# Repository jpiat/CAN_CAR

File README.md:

# CAN_CAR
Project for a RC car modded to be a mockup of a CAN bus for a real car

SCAD directory contains 3D models used for the motor encoder and parts mounting platform
PCB directory contains PCB designs for the Teensy CAN adapter and Arduin pro mini CAN adapter
SW directory contains code for both the CAN peripherals and main control unit

The main brain of the car is a Beaglebone green fitted with a CAN bus cape from Waveshare. The motor and steering servo control is performed by a teensy 3.1/2 fitted with a custom CAN board. Additional control units (collision sensors, headlights ...) will be added using arduino pro mini with CAN adapter.
The goal is to easily add sub-systems on the CAN bus to add functions ilke :
- line crossing detection
- vision-based road sign reading
- ...

Car base used for this project :
http://www.hobbyking.com/hobbyking/store/__24971__Turnigy_Trooper_SCT_4x4_1_10_Brushless_Short_Course_Truck_ARR_.html

The brushless motor and ESC are removed and replaced with a brushed 540 motor with H-bridge (easier to get full control of the motor)

H-bridge driver for the brushed motor

https://www.pololu.com/product/706 (cheaper eBay equivalent)

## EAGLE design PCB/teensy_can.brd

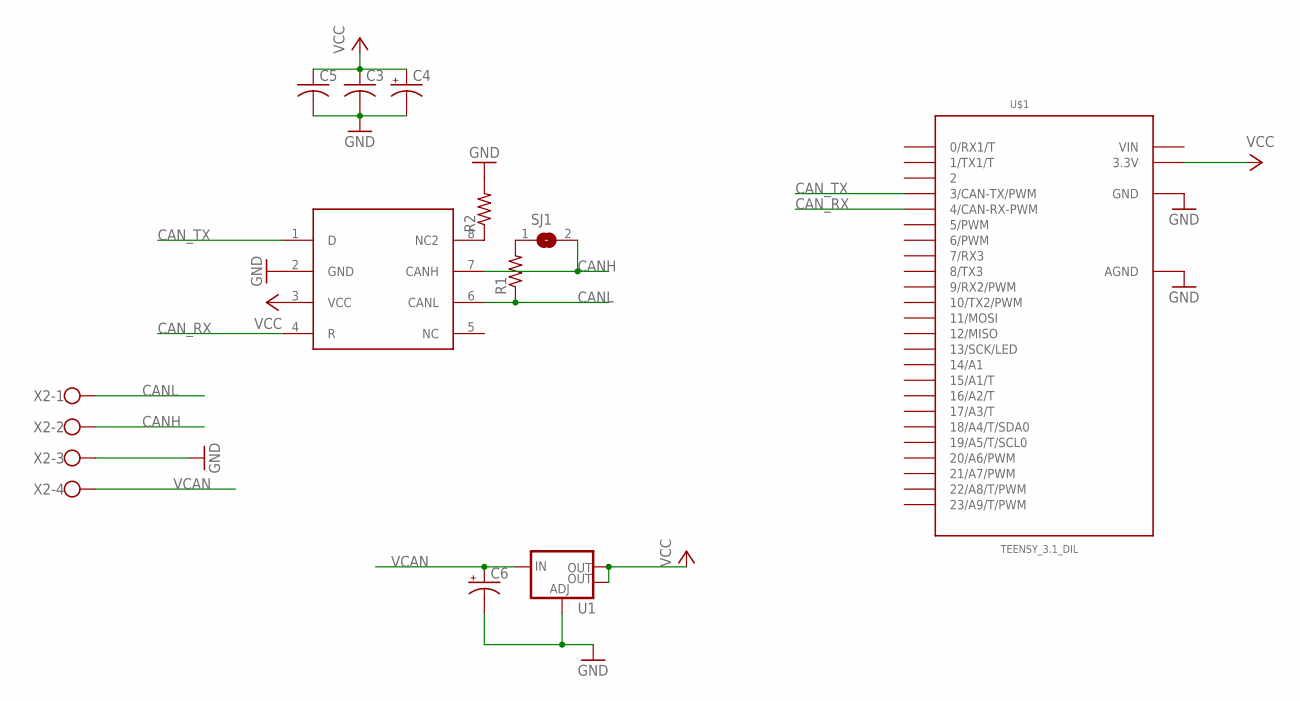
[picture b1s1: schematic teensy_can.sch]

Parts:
C3, C5: C-USC0805K; C0805K
C4, C6: CPOL-USA/3216-18R; A/3216-18R
R1, R2: R-US_R0805; R0805
SJ1: SJ
U1: V_REG_LM1117SOT223; SOT223
U$1: TEENSY_3.1_DIL; TEENSY3-DIL
U$2: SN65HVD232; SO08-SKINNYPADS
X2: W237-4

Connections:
CANH: SJ1.2, U$2.7 (CANH), X2.2
CANL: R1.1, U$2.6 (CANL), X2.1
CAN_RX: U$1.4 (4/CAN-RX-PWM), U$2.4 (R)
CAN_TX: U$1.3 (3/CAN-TX/PWM), U$2.1 (D)
GND: C3.2, C4.-, C5.2, C6.-, R2.2, U1.1 (ADJ), U$1.AGND, U$1.GND, U$2.2 (GND), X2.3
unnamed: R1.2, SJ1.1
unnamed: R2.1, U$2.8 (NC2)
VCAN: C6.+, U1.3 (IN), X2.4
VCC: C3.1, C4.+, C5.1, U1.2 (OUT), U1.4 (OUT), U$1.3.3V, U$2.3 (VCC)
VIN: U$1.VIN

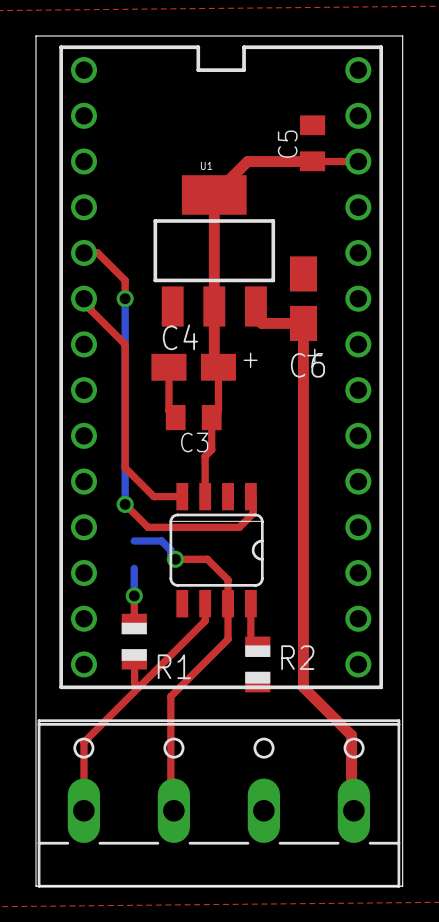
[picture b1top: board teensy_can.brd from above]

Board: 2 copper layers, 20.4 x 47.2 mm, 11 parts (1 on the bottom side), 9 nets.

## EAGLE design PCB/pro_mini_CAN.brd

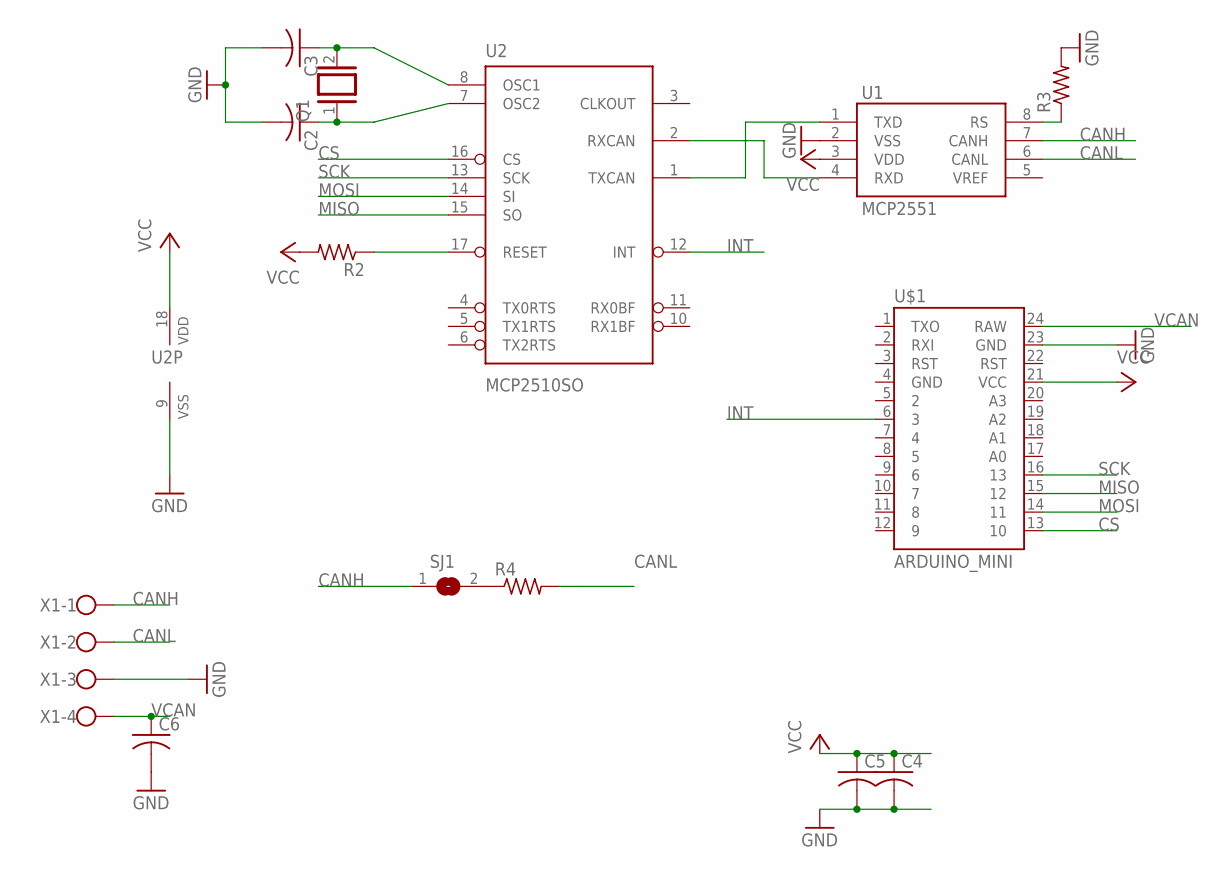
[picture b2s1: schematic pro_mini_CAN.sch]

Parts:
C2, C3, C4, C5, C6: C-USC0805K; C0805K
Q1: XTAL/S; QS
R2, R3, R4: R-US_R0805; R0805
SJ1: SJ
U1: MCP2551; SO08
U2: MCP2510SO; SO-18W
U$1: ARDUINO_MINI
X1: W237-4

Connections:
CANH: SJ1.1, U1.7 (CANH), X1.1
CANL: R4.2, U1.6 (CANL), X1.2
CS: U2.16 (CS), U$1.13 (10)
GND: C2.2, C3.2, C4.2, C5.2, C6.2, R3.2, U1.2 (VSS), U2.9 (VSS), U$1.23 (GND), X1.3
INT: U2.12 (INT), U$1.6 (3)
MISO: U2.15 (SO), U$1.15 (12)
MOSI: U2.14 (SI), U$1.14 (11)
unnamed: C3.1, Q1.2, U2.8 (OSC1)
unnamed: C2.1, Q1.1, U2.7 (OSC2)
unnamed: U1.1 (TXD), U2.1 (TXCAN)
unnamed: U1.4 (RXD), U2.2 (RXCAN)
unnamed: R2.1, U2.17 (RESET)
unnamed: R3.1, U1.8 (RS)
unnamed: R4.1, SJ1.2
SCK: U2.13 (SCK), U$1.16 (13)
VCAN: C6.1, U$1.24 (RAW), X1.4
VCC: C4.1, C5.1, R2.2, U1.3 (VDD), U2.18 (VDD), U$1.21 (VCC)

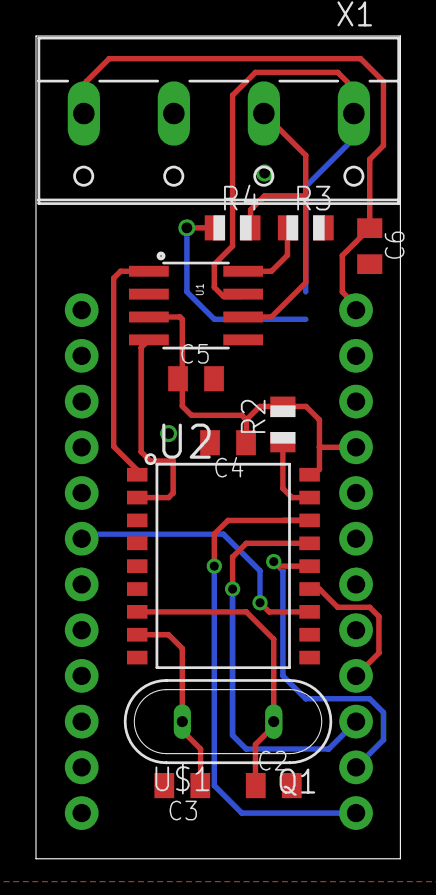
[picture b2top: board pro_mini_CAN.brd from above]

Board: 2 copper layers, 20.2 x 45.7 mm, 14 parts (1 on the bottom side), 17 nets.

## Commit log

2016-02-18 Starting the repository structure
2016-02-18 Added car model to the README
2016-02-18 Added new info to the Readme file
2016-02-18 Added stl file

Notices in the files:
parts and their libraries:
SparkFun-Boards: Licensing: Creative Commons ShareAlike 4.0 International - https://creativecommons.org/licenses/by-sa/4.0
